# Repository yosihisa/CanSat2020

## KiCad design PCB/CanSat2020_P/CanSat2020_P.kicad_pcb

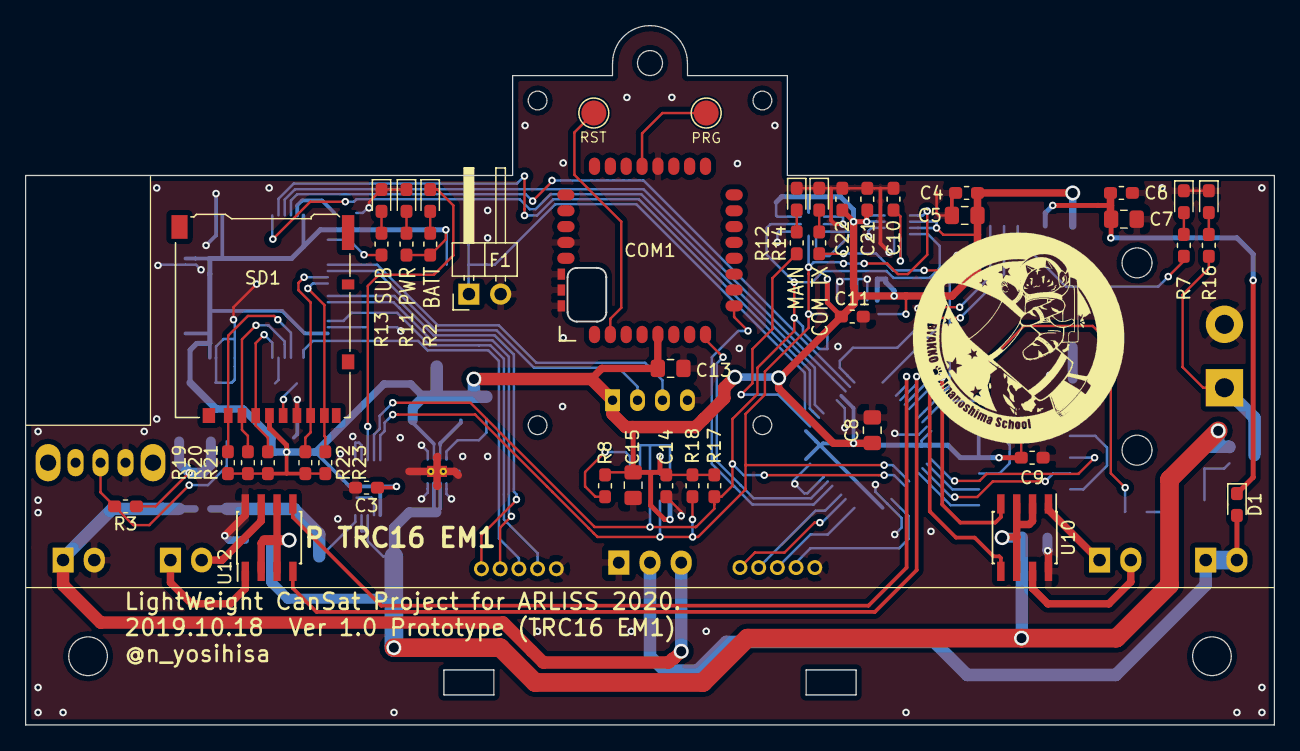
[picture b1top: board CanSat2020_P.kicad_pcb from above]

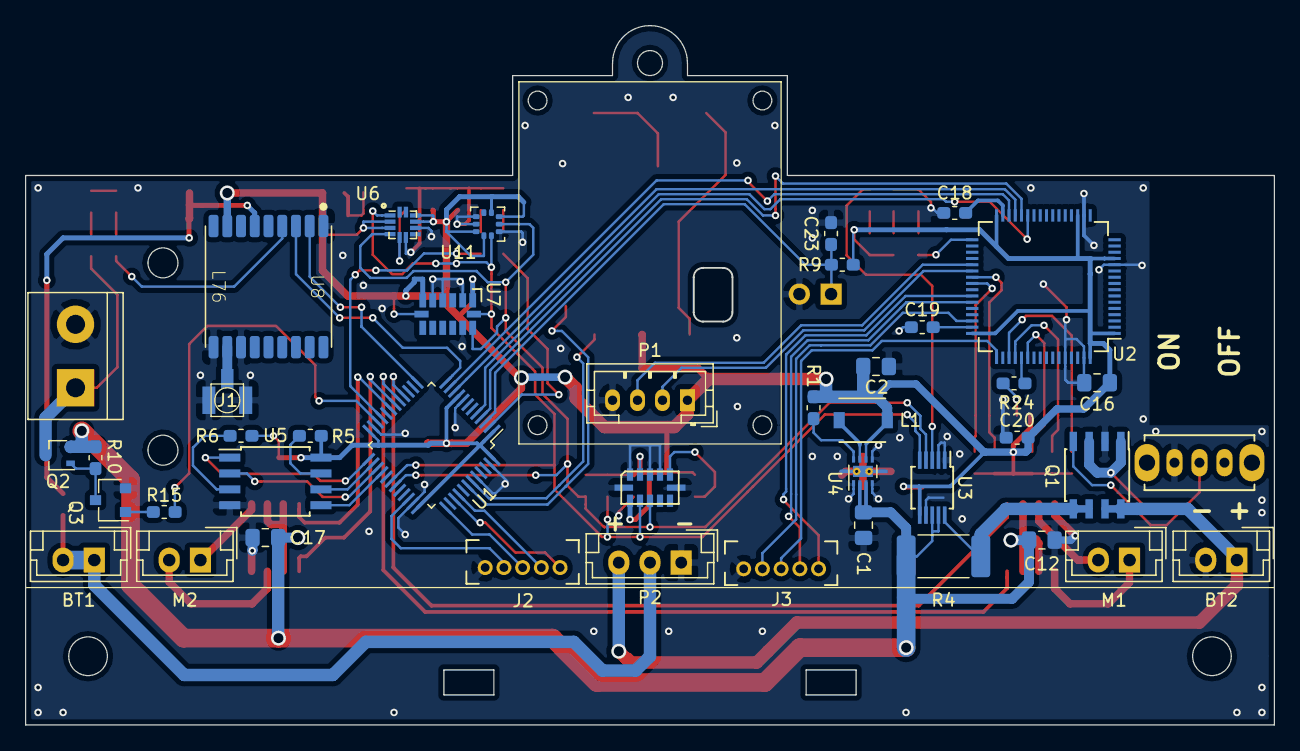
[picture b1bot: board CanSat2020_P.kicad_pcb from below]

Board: 2 copper layers, 100.0 x 56.0 mm, 87 parts (42 on the bottom side), 76 nets.

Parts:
BT1, BT2: battery; JST_EH_B02B-EH-A_1x02_P2.50mm_Vertical
C1, C2: 22u; C_0805_2012Metric_Pad1.15x1.40mm_HandSolder
C3, C4, C6, C9, C10, C11, C14, C20, C21, C22, C23: 0.1u; C_0603_1608Metric_Pad1.05x0.95mm_HandSolder
C5, C15: 4.7u; C_0805_2012Metric_Pad1.15x1.40mm_HandSolder
C7, C12, C13, C17: 10u; C_0805_2012Metric_Pad1.15x1.40mm_HandSolder
C8, C16: 1u; C_0805_2012Metric_Pad1.15x1.40mm_HandSolder
C18, C19: 2.2u; C_0603_1608Metric_Pad1.05x0.95mm_HandSolder
COM1: TWE_LITE_SMD; TWE-001L-SMD
D1: D_Small; D_0603_1608Metric_Pad1.05x0.95mm_HandSolder
F1: FLIGHT_PIN; PinHeader_1x02_P2.54mm_Horizontal
J1: GNSS Antenna; U.FL-R-SMT-1
J2: Debug_L0; STlink
J3: Debug_F2; STlink
L1: 2.2u; inductor_VLF4012-2R2
LED1: Alert; LED_0603_1608Metric_Pad1.05x0.95mm_HandSolder
LED2: P; LED_0603_1608Metric_Pad1.05x0.95mm_HandSolder
LED3: L0; LED_0603_1608Metric_Pad1.05x0.95mm_HandSolder
LED4: F2; LED_0603_1608Metric_Pad1.05x0.95mm_HandSolder
LED5: TX; LED_0603_1608Metric_Pad1.05x0.95mm_HandSolder
LED6: Nichrome; LED_0603_1608Metric_Pad1.05x0.95mm_HandSolder
LED7: 1PPS; LED_0603_1608Metric_Pad1.05x0.95mm_HandSolder
M1: Motor_L; JST_EH_B02B-EH-A_1x02_P2.50mm_Vertical
M2: Motor_R; JST_EH_B02B-EH-A_1x02_P2.50mm_Vertical
N1: NICHROME; TerminalBlock_bornier-2_P5.08mm
P1: C1098; JST_PH_B4B-PH-K_1x04_P2.00mm_Vertical
P2: Charge; JST_EH_B03B-EH-A_1x03_P2.50mm_Vertical
Q1: FDS4935A; SOIC-8_3.9x4.9mm_P1.27mm
Q2: MTM231102LBF; SOT-323_SC-70
Q3: 2SC2712; SC-59
R1: 100k; R_0603_1608Metric_Pad1.05x0.95mm_HandSolder
R2, R7, R11, R12, R13, R14, R16: 1k; R_0603_1608Metric_Pad1.05x0.95mm_HandSolder
R3, R5, R6, R8, R9, R10, R15: 10k; R_0603_1608Metric_Pad1.05x0.95mm_HandSolder
R4: 10m; R_2512_6332Metric_Pad1.52x3.35mm_HandSolder
R17, R18, R19, R20, R21, R22, R23: 2.2k; R_0603_1608Metric_Pad1.05x0.95mm_HandSolder
R24: 10; R_0603_1608Metric_Pad1.05x0.95mm_HandSolder
SD1: microSD; microSD_HC_Hirose_DM3AT-SF-PEJM5
SW1: POWER; SS-12D01-VG4
TP1: COM_RST; TestPoint_Pad_D2.0mm
TP2: COM_PRG; TestPoint_Pad_D2.0mm
U1: STM32L081CBTx; LQFP-48_7x7mm_P0.5mm
U2: STM32F205RFTx; LQFP-64_10x10mm_P0.5mm
U3: INA226; MSOP-10_3x3mm_P0.5mm
U4: TPS62162DSG; WSON-8-1EP_2x2mm_P0.5mm_EP0.9x1.6mm_ThermalVias
U5: W25Q128JVE; SOIJ-8_5.3x5.3mm_P1.27mm
U6: LSM303AGR; LGA-12_2x2mm_P0.5mm_HandSolder
U7: ADXL375; LGA_CC-14-1
U8: L76
U9: VL53L0X
U10, U12: BD6231F; SOIC-8_3.9x4.9mm_P1.27mm
U11: LPS25HB; ST_HLGA-10_2.5x2.5mm_P0.6mm_LayoutBorder3x2y

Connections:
+3V3: C2.1, C3.1, C4.1, C5.1, C8.1, C9.1, C11.1, C13.1, C14.1, C15.1, C16.1, C20.1, C21.1, C22.1, COM1.5, L1.2, P1.1, R1.2, R2.1, R5.2, R6.1, R8.2, R9.2, R11.1, R17.2, R18.1, R19.2, R20.2, R21.2, R22.2, R23.2, SD1.4, U1.1, U1.9, U1.24, U1.36, U1.48, U2.1, U2.13, U2.19, U2.32, U2.48, U2.64, U3.6, U4.6, U5.8, U6.2, U6.3, U6.9, U6.10, U7.1, U7.6, U7.7, U8.8, U9.2, U9.11, U11.1, U11.5, U11.6, U11.10
+4V: C6.1, C7.1, D1.1, U8.6
+BATT: C1.2, C12.1, C17.1, Q2.2, R4.2, R10.2, U3.8, U3.9, U4.2, U4.3, U10.2, U10.3, U10.6, U12.2, U12.3, U12.6
/CLK: U1.26, U5.6
/CMD: R21.1, SD1.3, U2.54
/CS: U1.25, U5.1
/DAT0: R22.1, SD1.7, U2.39
/DAT1: R23.1, SD1.8, U2.40
/DAT2: R19.1, SD1.1, U2.51
/DAT3: R20.1, SD1.2, U2.52
/FlightPin: C23.1, F1.1, R9.1, U1.3
/IMG_MODE: U1.5, U2.27
/LED_F2: R13.1, U2.33
/LED_L0: R12.1, U1.2
/LED_TX: R14.1, U1.21
/MAIN←SUB: U1.11, U2.30
/MAIN→SUB: U1.10, U2.29
/MISO: U1.27, U5.2
/MOSI: U1.28, U5.5
/MotorL_0: U1.16, U12.5
/MotorL_1: U1.17, U12.4
/MotorR_0: U1.18, U10.5
/MotorR_1: U1.19, U10.4
/Nichrome: R15.1, U1.22
/RX_F: J3.2, U2.43
/RX_L: J2.2, U1.40
/SCL: R18.2, U1.30, U3.5, U6.1, U7.14, U9.10, U11.2
/SCLK: R24.1, SD1.5
/SDA: R17.1, U1.31, U3.4, U6.4, U7.13, U9.9, U11.4
/STM←CAM: P1.2, U2.38
/STM←COM: COM1.8, U1.43
/STM←GNSS: U1.13, U8.2
/STM→CAM: P1.3, U2.37
/STM→COM: COM1.9, U1.42
/STM→GNSS: U1.12, U8.3
/SUB_EN: U1.4, U2.28
/SWCLK_F: J3.3, U2.49
/SWCLK_L: J2.3, U1.37
/SWDIO_F: J3.4, U2.46
/SWDIO_L: J2.4, U1.34
/TX_F: J3.1, U2.42
/TX_L: J2.1, U1.39
GND: BT2.2, C1.1, C2.2, C3.2, C4.2, C5.2, C6.2, C7.2, C8.2, C9.2, C10.2, C11.2, C12.2, C13.2, C14.2, C15.2, C16.2, C17.2, C18.2, C19.2, C20.2, C21.2, C22.2, C23.2, COM1.20, COM1.28, COM1.30, COM1.31, COM1.32, F1.2, J1.2, J2.5, J3.5, LED2.1, LED3.1, LED4.1, LED5.1, LED6.1, LED7.1, N1.2, P1.4, P2.1, Q1.2, Q3.2, SD1.6, SW1.1, U1.8, U1.23, U1.35, U1.44, U1.47, U2.12, U2.18, U2.60, U2.63, U3.1, U3.2, U3.7, U4.1, U4.4, U4.5, U4.9, U5.4, U6.6, U6.8, U7.2, U7.4, U7.5, U7.12, U8.1, U8.10, U8.12, U9.1, U9.3, U9.4, U9.6, U9.12, U10.8, U11.3, U11.8, U11.9, U12.8
unnamed: BT1.1, BT1.2, D1.2, P2.2
unnamed: BT2.1, P2.3, Q1.7, Q1.8
unnamed: C10.1, U6.5
unnamed: C18.1, U2.31
unnamed: C19.1, U2.47
unnamed: COM1.2, TP2.1
unnamed: COM1.21, TP1.1
unnamed: J1.1, U8.11
unnamed: L1.1, U4.7
unnamed: LED1.1, U3.3
unnamed: LED1.2, R2.2
unnamed: LED2.2, R11.2
unnamed: LED3.2, R12.2
unnamed: LED4.2, R13.2
unnamed: LED5.2, R14.2
unnamed: LED6.2, R16.2
unnamed: LED7.2, R7.2
unnamed: M1.1, U12.1
unnamed: M1.2, U12.7
unnamed: M2.1, U10.1
unnamed: M2.2, U10.7
unnamed: N1.1, Q2.3, R16.1
unnamed: Q1.1, Q1.3, R3.1
unnamed: Q1.4, R3.2, SW1.2
unnamed: Q1.5, Q1.6, R4.1, U3.10
unnamed: Q2.1, Q3.3, R10.1
unnamed: Q3.1, R15.2
unnamed: R1.1, U4.8
unnamed: R5.1, U5.7
unnamed: R6.2, U5.3
unnamed: R7.1, U8.4
unnamed: R8.1, U9.5
unnamed: R24.2, U2.53

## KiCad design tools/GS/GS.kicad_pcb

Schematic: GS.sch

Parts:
C1, C3: 10u; C_0805_2012Metric_Pad1.15x1.40mm_HandSolder
C2, C4, C7: 0.1u; C_0603_1608Metric_Pad1.05x0.95mm_HandSolder
C5, C6: 47p; C_0603_1608Metric_Pad1.05x0.95mm_HandSolder
CN1: USB-B-MICRO; Micro-USB
D1: PWR; LED_0603_1608Metric_Pad1.05x0.95mm_HandSolder
D2: TX; LED_0603_1608Metric_Pad1.05x0.95mm_HandSolder
D3: RX; LED_0603_1608Metric_Pad1.05x0.95mm_HandSolder
J1: SMA; SMA_Amphenol_901-144_Vertical
R1, R3, R4: 1K; R_0603_1608Metric_Pad1.05x0.95mm_HandSolder
R2: 10k; R_0603_1608Metric_Pad1.05x0.95mm_HandSolder
SW1: RST; SKRPACE010_kai
SW2: PRG; SKRPACE010_kai
TP1: ANT; TestPoint_THTPad_D3.0mm_Drill1.5mm
U1: L78L05_SOT89; SOT-89-3
U2: TWE_LITE_SMD; TWE-001L-SMD-noNTH
U3: FT231XQ; QFN-20-1EP_4x4mm_P0.5mm_EP2.5x2.5mm

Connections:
+3V3: C2.1, C3.1, C4.1, D1.2, D2.2, D3.2, R2.1, U1.1 (OUT), U2.5, U3.20
+5V: C1.2, C7.1, CN1.1, U1.3 (IN), U3.11, U3.12
/ANT: J1.1, TP1.1
/PRG: SW2.2, U2.2, U3.16
/RST: R2.2, SW1.2, U2.21, U3.7
/RXD: U2.8, U3.1
/TXD: U2.9, U3.17
GND: C1.1, C2.2, C3.2, C4.2, C5.1, C6.2, C7.2, CN1.5, CN1.6, CN1.7, J1.2, R1.2, SW1.1, SW2.1, U1.2 (GND), U2.20, U2.28, U2.30, U2.31, U2.32, U3.3, U3.13, U3.21
unnamed: C5.2, CN1.2, U3.9
unnamed: C6.1, CN1.3, U3.8
unnamed: D1.1, R1.1
unnamed: D2.1, R3.1
unnamed: D3.1, R4.1
unnamed: R3.2, U3.15
unnamed: R4.2, U3.14

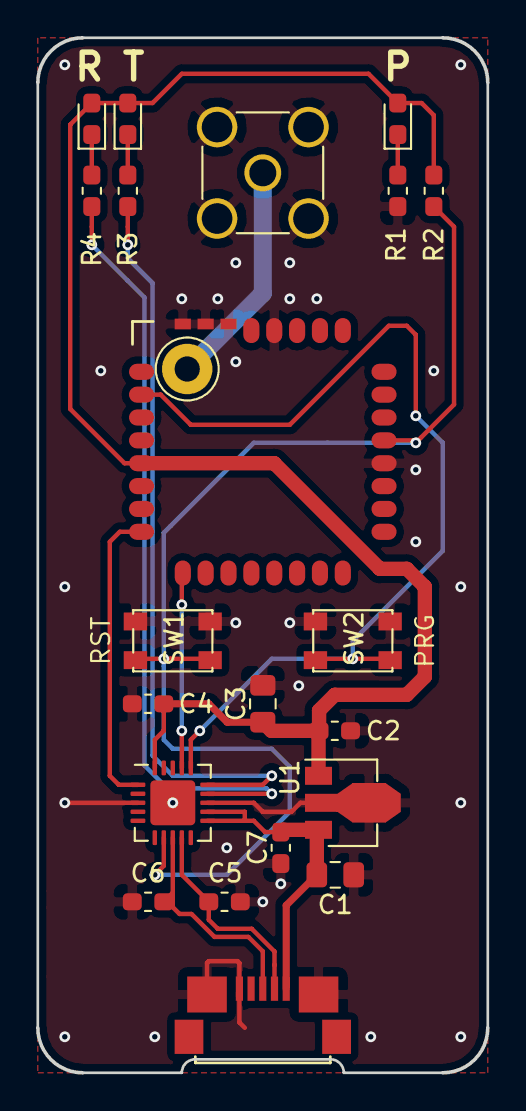
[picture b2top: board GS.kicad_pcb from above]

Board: 2 copper layers, 25.0 x 57.5 mm, 22 parts (0 on the bottom side), 15 nets.

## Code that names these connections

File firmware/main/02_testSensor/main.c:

#include "main.h"
#include "i2c.h"
#include "spi.h"
#include "tim.h"
#include "usart.h"
#include "gpio.h"

#include <stdio.h>
#include <string.h>

#include "cansat.h"
#include "CUI.h"

void SystemClock_Config(void);

static img_t img_data = {0};
static uint8_t sub_rx_buff[11] = {0};
static cansat_t cansat_data;

void __io_putchar(uint8_t ch)
{
  HAL_UART_Transmit(&huart5, &ch, 1, 1);
  HAL_UART_Transmit(&huart1, &ch, 1, 1); //COM
}

void HAL_GPIO_EXTI_Callback(uint16_t GPIO_Pin)
{
  for (int i = 0; i < 10; i++)
  {
    HAL_UART_Receive(&huart4, &sub_rx_buff[0], 1, 50);
    if (sub_rx_buff[0] == '$')
      break;
  }
  HAL_UART_Receive(&huart4, &sub_rx_buff[0], 11, 50);
  if (sub_rx_buff[0] == 'O')
  {
    img_data.name = (sub_rx_buff[1] << 8) + sub_rx_buff[2];
    img_data.xc = (sub_rx_buff[3] << 8) + sub_rx_buff[4];
    img_data.yc = (sub_rx_buff[5] << 8) + sub_rx_buff[6];
    img_data.s = (sub_rx_buff[7] << 16) + (sub_rx_buff[8] << 8) + sub_rx_buff[9];
  }
  else if (sub_rx_buff[0] == 'o')
  {
    img_data.name = (sub_rx_buff[2] << 8) + sub_rx_buff[3];
    img_data.xc = (sub_rx_buff[4] << 8) + sub_rx_buff[5];
    img_data.yc = (sub_rx_buff[6] << 8) + sub_rx_buff[7];
    img_data.s = (sub_rx_buff[8] << 16) + (sub_rx_buff[9] << 8) + sub_rx_buff[10];
  }
  else
  {
    return;
  }
}

void HAL_TIM_PeriodElapsedCallback(TIM_HandleTypeDef *htim)
{
  if (htim == &htim2)
  {
    _motor(&cansat_data.motor, cansat_data.voltage);
  }
}
int main(void)
{
  /* USER CODE BEGIN 1 */

  /* USER CODE END 1 */
  

  /* MCU Configuration--------------------------------------------------------*/

  /* Reset of all peripherals, Initializes the Flash interface and the Systick. */
  HAL_Init();

  /* USER CODE BEGIN Init */

  /* USER CODE END Init */

  /* Configure the system clock */
  SystemClock_Config();

  /* USER CODE BEGIN SysInit */

  /* USER CODE END SysInit */

  /* Initialize all configured peripherals */
  MX_GPIO_Init();
  MX_I2C1_Init();
  MX_SPI2_Init();
  MX_TIM3_Init();
  MX_USART1_UART_Init();
  MX_USART2_UART_Init();
  MX_USART4_UART_Init();
  MX_USART5_UART_Init();
  MX_TIM2_Init();
  /* USER CODE BEGIN 2 */


  //---------------------------------------Initialization BEGIN------------------------------------------------
  HAL_NVIC_DisableIRQ(EXTI4_15_IRQn);

  ///HAL_GPIO_WritePin(SUB_EN_GPIO_Port, SUB_EN_Pin, GPIO_PIN_RESET);  //SUB Disable
  HAL_GPIO_WritePin(SUB_MODE_GPIO_Port, SUB_MODE_Pin, GPIO_PIN_SET);//SUB Mode PINK

  HAL_Delay(500);

  printf("Hello Main MCU Sensor test!\n");
  HAL_GPIO_WritePin(LED_L0_GPIO_Port, LED_L0_Pin, GPIO_PIN_SET);
  HAL_GPIO_WritePin(LED_TX_GPIO_Port, LED_TX_Pin, GPIO_PIN_SET);
  HAL_GPIO_WritePin(Nichrome_GPIO_Port, Nichrome_Pin, GPIO_PIN_SET);

  HAL_Delay(200);

  HAL_GPIO_WritePin(LED_L0_GPIO_Port, LED_L0_Pin, GPIO_PIN_RESET);
  HAL_GPIO_WritePin(LED_TX_GPIO_Port, LED_TX_Pin, GPIO_PIN_RESET);
  HAL_GPIO_WritePin(Nichrome_GPIO_Port, Nichrome_Pin, GPIO_PIN_RESET);

  printf("INA226  = %02X\n", ina226_who_am_i());
  printf("LPS25HB = %01X\n", lps25h_who_am_i());
  printf("ADXL375 = %01X\n", adxl375_who_am_i());
  printf("JEDECID = %lX\n", flash_read_ID());

  init_I2C();
  init_gnss();
  init_pwm(&cansat_data.motor);

  update_sensor(&cansat_data);

  cansat_data.press_lpf = cansat_data.press;
  cansat_data.press_d = 0;
  cansat_data.press_d_lpf = 0;
  cansat_data.press_d_raw = 0;

  printf("TIME %02d:%02d:%02d\n", cansat_data.gnss.hh, cansat_data.gnss.mm, cansat_data.gnss.ss);
  set_goalFromEEPROM(0);

  cansat_data.flash_address = get_startAddress(cansat_data.gnss.hh, cansat_data.gnss.mm, cansat_data.gnss.ss);
  cansat_data.log_num = 0;
  printf("Flash address 0x%lX\n", cansat_data.flash_address);

  HAL_NVIC_EnableIRQ(EXTI4_15_IRQn);
  HAL_TIM_Base_Start_IT(&htim2);
  //---------------------------------------Initialization END------------------------------------------------

  /* USER CODE END 2 */

  /* Infinite loop */
  /* USER CODE BEGIN WHILE */
  while (1)
  {
    /* USER CODE END WHILE */

    /* USER CODE BEGIN 3 */
	/*  if (cansat_data.log_num < 20) {
		  motor_Speed(&cansat_data.motor, 100, 0);
	  }
	  else if (cansat_data.log_num < 40) {
		  motor_Speed(&cansat_data.motor, -100, 0);
	  }
	  else if (cansat_data.log_num < 60) {
		  motor_Speed(&cansat_data.motor, 0, 100);
	  }
	  else if (cansat_data.log_num < 80) {
		  motor_Speed(&cansat_data.motor, 0, -100);
	  }
	  else
	  if (cansat_data.log_num > 100) {
		  motor_Speed(&cansat_data.motor, 100, 100);
	  }*/

	  //Enter CUI Mode
	  if (get_char(20) == 'q') {
		  HAL_NVIC_DisableIRQ(EXTI4_15_IRQn);
		  HAL_TIM_Base_Stop_IT(&htim2);
		  motorStop();

		  CUI_main();

		  HAL_NVIC_EnableIRQ(EXTI4_15_IRQn);
		  HAL_TIM_Base_Start_IT(&htim2);
	  };


	  HAL_GPIO_WritePin(LED_L0_GPIO_Port, LED_L0_Pin, GPIO_PIN_SET);
	  update_sensor(&cansat_data);
	  cansat_data.img = img_data;

	  write_log(&cansat_data);

	  HAL_GPIO_WritePin(LED_L0_GPIO_Port, LED_L0_Pin, GPIO_PIN_RESET);

	  if (cansat_data.log_num == 50) {
		  HAL_GPIO_WritePin(SUB_MODE_GPIO_Port, SUB_MODE_Pin, GPIO_PIN_RESET); //SUB Mode RED
	  }
  }
  /* USER CODE END 3 */
}

/**
  * @brief System Clock Configuration
  * @retval None
  */
void SystemClock_Config(void)
{
  RCC_OscInitTypeDef RCC_OscInitStruct = {0};
  RCC_ClkInitTypeDef RCC_ClkInitStruct = {0};
  RCC_PeriphCLKInitTypeDef PeriphClkInit = {0};

  /** Configure the main internal regulator output voltage 
  */
  __HAL_PWR_VOLTAGESCALING_CONFIG(PWR_REGULATOR_VOLTAGE_SCALE1);
  /** Initializes the CPU, AHB and APB busses clocks 
  */
  RCC_OscInitStruct.OscillatorType = RCC_OSCILLATORTYPE_HSI;
  RCC_OscInitStruct.HSIState = RCC_HSI_ON;
  RCC_OscInitStruct.HSICalibrationValue = RCC_HSICALIBRATION_DEFAULT;
  RCC_OscInitStruct.PLL.PLLState = RCC_PLL_ON;
  RCC_OscInitStruct.PLL.PLLSource = RCC_PLLSOURCE_HSI;
  RCC_OscInitStruct.PLL.PLLMUL = RCC_PLLMUL_4;
  RCC_OscInitStruct.PLL.PLLDIV = RCC_PLLDIV_2;
  if (HAL_RCC_OscConfig(&RCC_OscInitStruct) != HAL_OK)
  {
    Error_Handler();
  }
  /** Initializes the CPU, AHB and APB busses clocks 
  */
  RCC_ClkInitStruct.ClockType = RCC_CLOCKTYPE_HCLK|RCC_CLOCKTYPE_SYSCLK
                              |RCC_CLOCKTYPE_PCLK1|RCC_CLOCKTYPE_PCLK2;
  RCC_ClkInitStruct.SYSCLKSource = RCC_SYSCLKSOURCE_PLLCLK;
  RCC_ClkInitStruct.AHBCLKDivider = RCC_SYSCLK_DIV1;
  RCC_ClkInitStruct.APB1CLKDivider = RCC_HCLK_DIV1;
  RCC_ClkInitStruct.APB2CLKDivider = RCC_HCLK_DIV1;

  if (HAL_RCC_ClockConfig(&RCC_ClkInitStruct, FLASH_LATENCY_1) != HAL_OK)
  {
    Error_Handler();
  }
  PeriphClkInit.PeriphClockSelection = RCC_PERIPHCLK_USART1|RCC_PERIPHCLK_USART2
                              |RCC_PERIPHCLK_I2C1;
  PeriphClkInit.Usart1ClockSelection = RCC_USART1CLKSOURCE_PCLK2;
  PeriphClkInit.Usart2ClockSelection = RCC_USART2CLKSOURCE_PCLK1;
  PeriphClkInit.I2c1ClockSelection = RCC_I2C1CLKSOURCE_PCLK1;
  if (HAL_RCCEx_PeriphCLKConfig(&PeriphClkInit) != HAL_OK)
  {
    Error_Handler();
  }
}

/**
  * @brief  This function is executed in case of error occurrence.
  * @retval None
  */
void Error_Handler(void)
{
  /* USER CODE BEGIN Error_Handler_Debug */
  /* User can add his own implementation to report the HAL error return state */

  /* USER CODE END Error_Handler_Debug */
}

#ifdef  USE_FULL_ASSERT
/**
  * @brief  Reports the name of the source file and the source line number
  *         where the assert_param error has occurred.
  * @param  file: pointer to the source file name
  * @param  line: assert_param error line source number
  * @retval None
  */
void assert_failed(uint8_t *file, uint32_t line)
{ 
  /* USER CODE BEGIN 6 */
  /* User can add his own implementation to report the file name and line number,
     tex: printf("Wrong parameters value: file %s on line %d\r\n", file, line) */
  /* USER CODE END 6 */
}
#endif /* USE_FULL_ASSERT */

/************************ (C) COPYRIGHT STMicroelectronics *****END OF FILE****/

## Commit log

2019-10-12 Add main,sub 初期コード
2019-10-12 Add ReadMe
2019-10-16 Add schematic
2019-10-16 Update Pin assignment
2019-10-16 Add LPS25HBTR
2019-10-17 Update PCB
2019-10-18 Add GS
2019-10-29 Update GS
2019-10-29 Update PCB
    TRC16 EM1 発注
2019-10-29 Add main_sensor_test
    INA226動作確認
2019-10-29 Update main_sensor_test (LPS25HB)
2019-10-30 Update main_sensor_test (ADXL375)
2019-10-31 Update main_sensor_test (LSM303)
2019-10-31 VL53L0Xが使えなかった
2019-10-31 Update sensor_test
2019-10-31 Add main_UART
    NMEA確認 TWELITE書き込み用
2019-11-01 Update main_sensor_test(GNSS)
2019-11-02 Updata SUB
2019-11-02 Updata SUB (浮動小数点演算の廃止)
2019-11-02 Add HSV_setting_tool
2019-11-03 Add SD logger
2019-11-03 Update Transmit Image Data
2019-11-03 Fixed UART RX Interrupt
2019-11-11 test flash
2019-11-13 Add EEPROM Access
2019-11-13 Add PWM
2019-12-12 update save flash
2019-12-12 Update Source.cpp
    2色に対応
2019-12-13 Update Save LOG ,print LOG
2019-12-17 Update CUI
    CUIの機能が一通り完成した！
2019-12-17 Fixed delete_log
2019-12-19 Update press
2019-12-19 Merged main
2019-12-19 Add gnc
2019-12-21 走行試験(1221)
2019-12-22 log 修正
2019-12-22 速度推定 パラメータ更新
2019-12-25 開発環境の変更
2019-12-26 Create CanSar2020.code-workspace
2019-12-26 Update Optical Navigation
2020-02-12 モータ大型化に対応
2020-02-14 画像認識 パラメータ調整
2020-12-29 環境構築メモ追加
